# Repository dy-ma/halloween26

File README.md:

# Halloween 2026

The integrated wireless show controller, motor-node firmware, simulator, and Pi
control panel live in [`sync/`](sync/README.md). The original sketches remain
available as isolated hardware tests.

Hardware, software, and build notes for our Halloween 2026 props. This repository holds multiple boards and projects; each has its own directory, README, and design status.

## Projects

| Project | Purpose | Status |
|---|---|---|
| [Base controller](base-controller/README.md) | ESP32-C6 controller for the tractor mechanism, with external stepper-driver control, limit inputs, and onboard power conversion | Initial PCB design complete; verification in progress; not hardware-tested |
| [Baby's first PCB](babys-first/README.md) | Small LED board used to learn KiCad | Practice project; not intended for manufacture |
| [FX audio](fx/README.md) | Rust library providing play-a-file-on-a-device, plus a thin CLI for PipeWire and Bluetooth testing | Initial programmable primitive |
| [Cue firmware](firmware/README.md) | Shared cue messages and non-blocking ESP-NOW transport for button nodes and the Pi serial gateway | Initial refactor; hardware verification pending |

Additional boards can be added alongside these when ready. See [adding a board](docs/adding-a-board.md) for the directory convention.

## Repository layout

```text
halloween26/
├── README.md                 Project index
├── docs/                     Shared repository and release conventions
├── base-controller/
│   ├── README.md             Board overview and status
│   ├── CHANGELOG.md          Board revision notes
│   ├── *.kicad_*             Editable KiCad design
│   ├── docs/                 Architecture, parts, checks, and design history
│   ├── libraries/            Board-specific symbols and footprints
│   ├── previews/             Selected design images
│   └── scripts/              Board-specific build helpers
├── babys-first/              KiCad practice board
├── LICENSE                   Original hardware/design-documentation license
├── LICENSES/                 Additional license texts
└── NOTICE.md                 Attribution and third-party terms
```

Board-specific decisions and instructions belong with that board. The root `docs/` folder is for guidance shared across projects. Open a board's README for its KiCad version, pinouts, build commands, and verification status.

## Releases

Editable sources live in Git. Gerbers, drill files, and other generated manufacturing files are attached manually to [GitHub Releases](https://github.com/dy-ma/halloween26/releases), using board-specific tags such as `base-controller-v0.1.0`. There are no automatic release workflows.

See [the shared release conventions](docs/releases.md) and each board's release instructions. A design being present here does not mean it is ready to manufacture; check that project's status first.

## License

Original hardware and design documentation: [CERN-OHL-P-2.0](LICENSE). Original scripts: [MIT](LICENSES/MIT.txt). Imported libraries retain their upstream terms; see [NOTICE.md](NOTICE.md).

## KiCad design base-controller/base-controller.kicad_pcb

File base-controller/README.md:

# Base controller — tractor motion control

A KiCad learning project for a wireless, chain-driven Halloween tractor prop. A Seeed XIAO ESP32-C6 controls an external DM542-class stepper driver, reads two limit switches, and exposes spare I/O and test points. The board includes 24 V power distribution, a protected logic branch, and a 24 V-to-5 V converter.

**Initial design complete; verification in progress. Not ready to order.** The 92 × 69 mm, two-layer PCB is routed. Checks on 2026-09-20 report zero ERC issues, zero unconnected PCB items, and zero schematic/PCB mismatches. PCB DRC also passes with zero errors or warnings after updating U3’s thermal-via footprint. There has been no hardware bring-up. See the [verification checklist](docs/verification.md).

## Open the design

Use **KiCad 9.0.6** with its standard symbol and footprint libraries installed. Open [base-controller.kicad_pro](base-controller.kicad_pro) in KiCad's project manager, then open the schematic or PCB.

Project-local `Halloween` libraries are registered through checked-in, project-relative library tables. No global custom-library setup should be needed. Some parts lack 3D models; that does not mean their PCB footprint is missing.

| Directory | Contents |
|---|---|
| [`docs/`](docs/) | Architecture, parts, decisions, verification, and release procedure |
| [`docs/history/`](docs/history/) | Earlier schematic, placement, and routing notes |
| [`libraries/`](libraries/) | Project-local symbols and footprints with provenance |
| [`previews/`](previews/) | Selected board and layout images |
| [`scripts/`](scripts/) | Optional local KiCad checks and manufacturing export helper |

See the [board changelog](CHANGELOG.md) for revision notes and the [repository overview](../README.md) for other boards.

## Design reference

- [Architecture, connector pinouts, GPIO map, and rationale](docs/architecture.md)
- [Parts list and JLC links](docs/parts-list.md)
- [Power protection and driver-interface decisions](docs/electrical-decisions.md)
- [External power supplies, inline fuse, and cable recommendations](docs/non-pcb-components.md)
- [Library provenance and changes](libraries/README.md)
- [Sourcing research](docs/parts-sourcing.md) — dated stock snapshots, including superseded candidates
- [Historical schematic review](docs/history/schematic-review-notes.md) — not the current issue list

The controller uses **24 V nominal input**. Motor supply power passes through to J7; the onboard eFuse protects the logic branch only. Remove **J6** before using USB with external power. The DM542 driver, motor, power supply, inline fuse, mechanics, firmware, and audio controller are external to this PCB. The 5 A pass-through figure is a design target, not a tested rating.

## Checks and releases

Save the project, then optionally run **from the repository root**:

```sh
python3 base-controller/scripts/build_hardware.py check
```

This checks a copy, refills zones, runs ERC/DRC and schematic parity, and produces review files under `build/base-controller/check/`. The current design passes these automated checks; the manual verification checklist still applies. It does not modify your KiCad sources.

Gerbers and drill files belong in **GitHub Releases**, not the source tree. Releases are prepared manually; there is no GitHub Actions workflow. Follow [the release procedure](docs/releases.md) to use either KiCad's GUI or the local script, inspect the outputs, and attach ZIPs to a tagged release.

The printed QR code points to [the future project article](https://www.dyma.dev/articles/tractor-driver).

## License

Original hardware and design documentation: [CERN-OHL-P-2.0](../LICENSE). Original scripts: [MIT](../LICENSES/MIT.txt). Imported library material keeps its upstream licenses; see [NOTICE.md](../NOTICE.md).

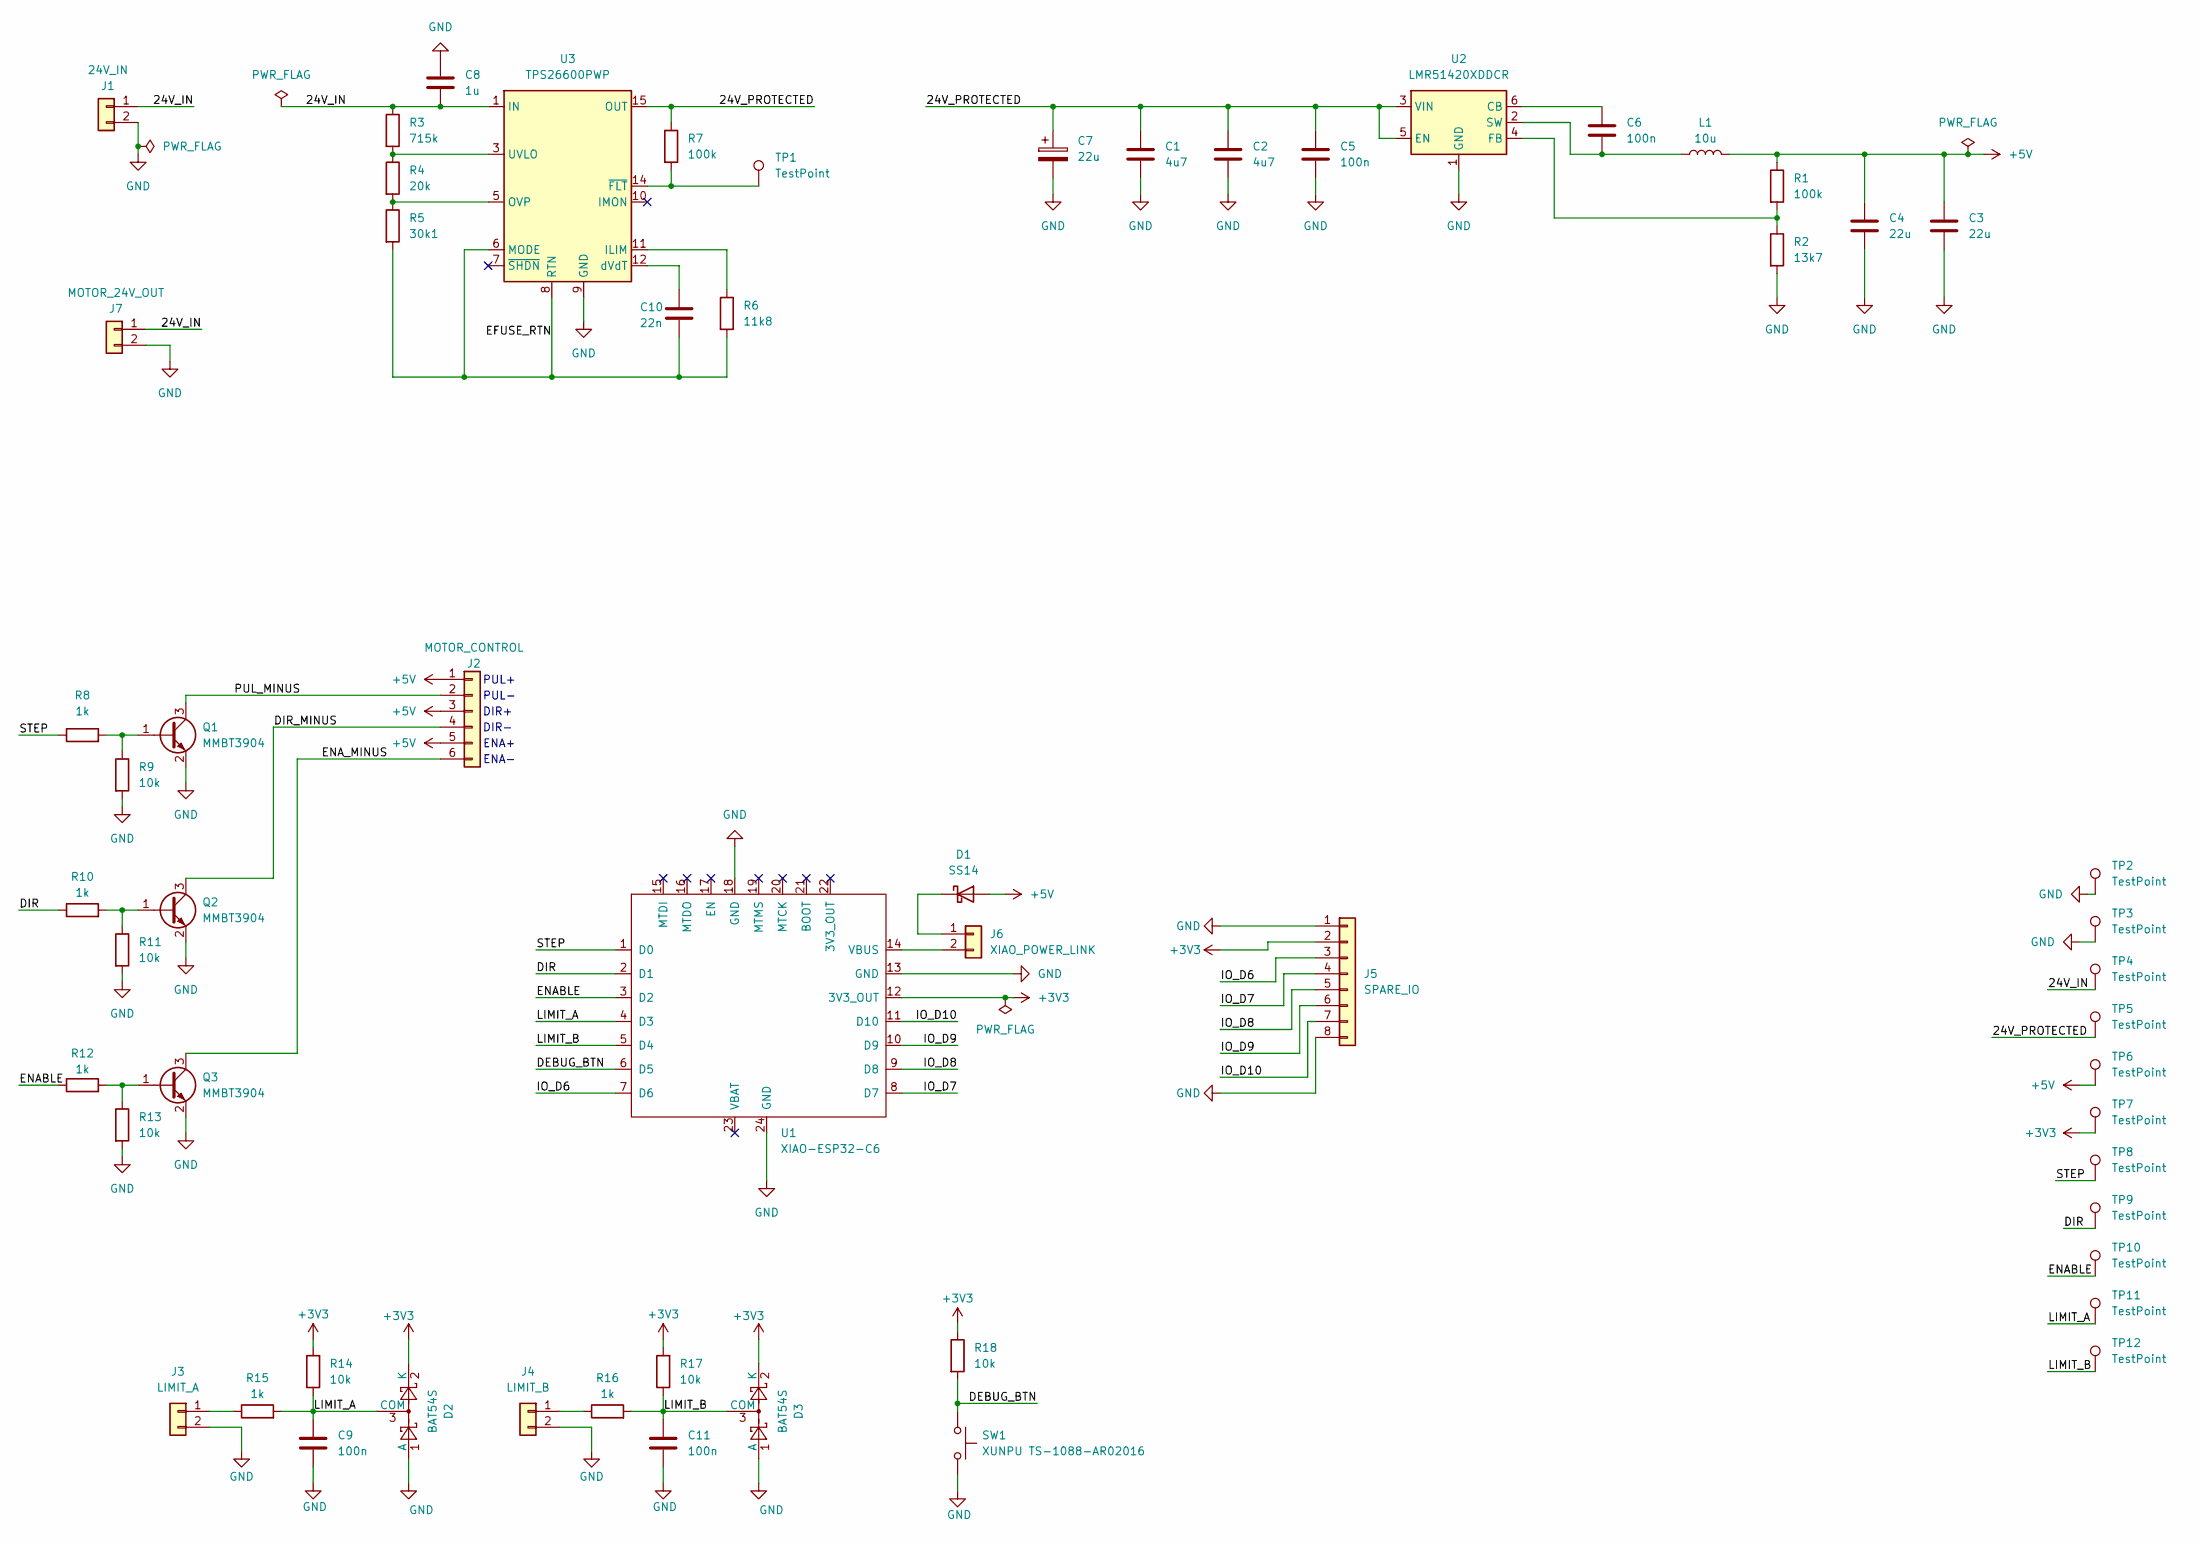
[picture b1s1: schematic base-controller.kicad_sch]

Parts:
C1, C2: 4u7; C_1206_3216Metric; MPN CL31B475KBHNNNE; LCSC C51205
C3, C4: 22u; C_1206_3216Metric; MPN CL31A226KAHNNNE; LCSC C12891
C5, C6, C9, C11: 100n; C_0603_1608Metric; MPN CC0603KRX7R9BB104; LCSC C14663
C7: 22u; CP_Elec_6.3x5.4; MPN RVT1H220M0605; LCSC C27783
C8: 1u; C_0805_2012Metric; MPN CL21B105KBFNNNE; LCSC C28323
C10: 22n; C_0603_1608Metric; MPN CL10B223KB8NNNC; LCSC C21122
D1: SS14; D_SMA; MPN SS14; LCSC C2480
D2, D3: BAT54S; SOT-23; MPN BAT54S KL4; LCSC C8592
J1: 24V_IN; Molex_Micro-Fit_3.0_43650-0215_1x02_P3.00mm_Vertical; MPN 436500215; LCSC C293740
J2: MOTOR_CONTROL; JST_XH_S6B-XH-A_1x06_P2.50mm_Horizontal; MPN S6B-XH-A(LF)(SN); LCSC C157919
J3: LIMIT_A; JST_XH_S2B-XH-A_1x02_P2.50mm_Horizontal; MPN S2B-XH-A(LF)(SN); LCSC C157931
J4: LIMIT_B; JST_XH_S2B-XH-A_1x02_P2.50mm_Horizontal; MPN S2B-XH-A(LF)(SN); LCSC C157931
J5: SPARE_IO; PinHeader_1x08_P2.54mm_Vertical; MPN PZ254V-11-08P; LCSC C492407
J6: XIAO_POWER_LINK; PinHeader_1x02_P2.54mm_Vertical; MPN PZ254V-11-02P; LCSC C492401
J7: MOTOR_24V_OUT; Molex_Micro-Fit_3.0_43650-0215_1x02_P3.00mm_Vertical; MPN 436500215; LCSC C293740
L1: 10u; L_Sunlord_MWSA0804S; MPN MWSA0804S-100MT; LCSC C17700171
Q1, Q2, Q3: MMBT3904; SOT-23; MPN MMBT3904(RANGE:100-300); LCSC C20526
R1, R7: 100k; R_0603_1608Metric; MPN 0603WAF1003T5E; LCSC C25803
R2: 13k7; R_0603_1608Metric; MPN 0603WAF1372T5E; LCSC C22793
R3: 715k; R_0603_1608Metric; MPN RC0603FR-07715KL; LCSC C137685
R4: 20k; R_0603_1608Metric; MPN 0603WAF2002T5E; LCSC C4184
R5: 30k1; R_0603_1608Metric; MPN 0603WAF3012T5E; LCSC C23000
R6: 11k8; R_0603_1608Metric; MPN 0603WAF1182T5E; LCSC C22861
R8, R10, R12, R15, R16: 1k; R_0603_1608Metric; MPN 0603WAF1001T5E; LCSC C21190
R9, R11, R13, R14, R17, R18: 10k; R_0603_1608Metric; MPN 0603WAF1002T5E; LCSC C25804
SW1: XUNPU TS-1088-AR02016; SW_SPST_TS-1088-xR020; MPN TS-1088-AR02016; LCSC C720477
TP1, TP2, TP3, TP4, TP5, TP6, TP7, TP8, TP9, TP10, TP11, TP12: TestPoint; TestPoint_Pad_D2.0mm
U1: XIAO-ESP32-C6; XIAO-ESP32-C6-SMD; MPN 113991254; LCSC C27675191
U2: LMR51420XDDCR; TSOT-23-6; MPN LMR51420XDDCR; LCSC C5246146
U3: TPS26600PWP; TPS26600_HTSSOP16_ThermalVias_0.3mm; MPN TPS26600PWPR; LCSC C544399

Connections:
+3V3: D2.2 (K), D3.2 (K), J5.2, R14.2, R17.2, R18.1, TP7.1, U1.12 (3V3_OUT)
+5V: C3.1, C4.1, D1.2 (A), J2.1, J2.3, J2.5, L1.2, R1.1, TP6.1
/24V_IN: C8.1, J1.1, J7.1, R3.1, TP4.1, U3.1 (IN), U3.2 (IN)
/24V_PROTECTED: C1.1, C2.1, C5.1, C7.1, R7.1, TP5.1, U2.3 (VIN), U2.5 (EN), U3.15 (OUT), U3.16 (OUT)
/DEBUG_BTN: R18.2, SW1.1, U1.6 (D5)
/DIR: R10.1, TP9.1, U1.2 (D1)
/DIR_MINUS: J2.4, Q2.3 (C)
/EFUSE_RTN: C10.2, R5.2, R6.2, U3.6 (MODE), U3.8 (RTN), U3.17 (RTN)
/ENABLE: R12.1, TP10.1, U1.3 (D2)
/ENA_MINUS: J2.6, Q3.3 (C)
/IO_D6: J5.3, U1.7 (D6)
/IO_D7: J5.4, U1.8 (D7)
/IO_D8: J5.5, U1.9 (D8)
/IO_D9: J5.6, U1.10 (D9)
/IO_D10: J5.7, U1.11 (D10)
/LIMIT_A: C9.1, D2.3 (COM), R14.1, R15.2, TP11.1, U1.4 (D3)
/LIMIT_B: C11.1, D3.3 (COM), R16.2, R17.1, TP12.1, U1.5 (D4)
/PUL_MINUS: J2.2, Q1.3 (C)
/STEP: R8.1, TP8.1, U1.1 (D0)
GND: C1.2, C2.2, C3.2, C4.2, C5.2, C7.2, C8.2, C9.2, C11.2, D2.1 (A), D3.1 (A), J1.2, J3.2, J4.2, J5.1, J5.8, J7.2, Q1.2 (E), Q2.2 (E), Q3.2 (E), R2.2, R9.2, R11.2, R13.2, SW1.2, TP2.1, TP3.1, U1.13 (GND), U1.18 (GND), U1.24 (GND), U2.1 (GND), U3.9 (GND)
unnamed: D1.1 (K), J6.1
unnamed: J3.1, R15.1
unnamed: J4.1, R16.1
unnamed: J6.2, U1.14 (VBUS)
unnamed: Q1.1 (B), R8.2, R9.1
unnamed: Q2.1 (B), R10.2, R11.1
unnamed: Q3.1 (B), R12.2, R13.1
unnamed: C6.1, U2.6 (CB)
unnamed: R1.2, R2.1, U2.4 (FB)
unnamed: C6.2, L1.1, U2.2 (SW)
unnamed: R6.1, U3.11 (ILIM)
unnamed: R4.2, R5.1, U3.5 (OVP)
unnamed: R3.2, R4.1, U3.3 (UVLO)
unnamed: C10.1, U3.12 (dVdT)
unnamed: R7.2, TP1.1, U3.14 (~FLT)

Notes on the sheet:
ENA-
PUL+
DIR+
PUL-
DIR-
ENA+

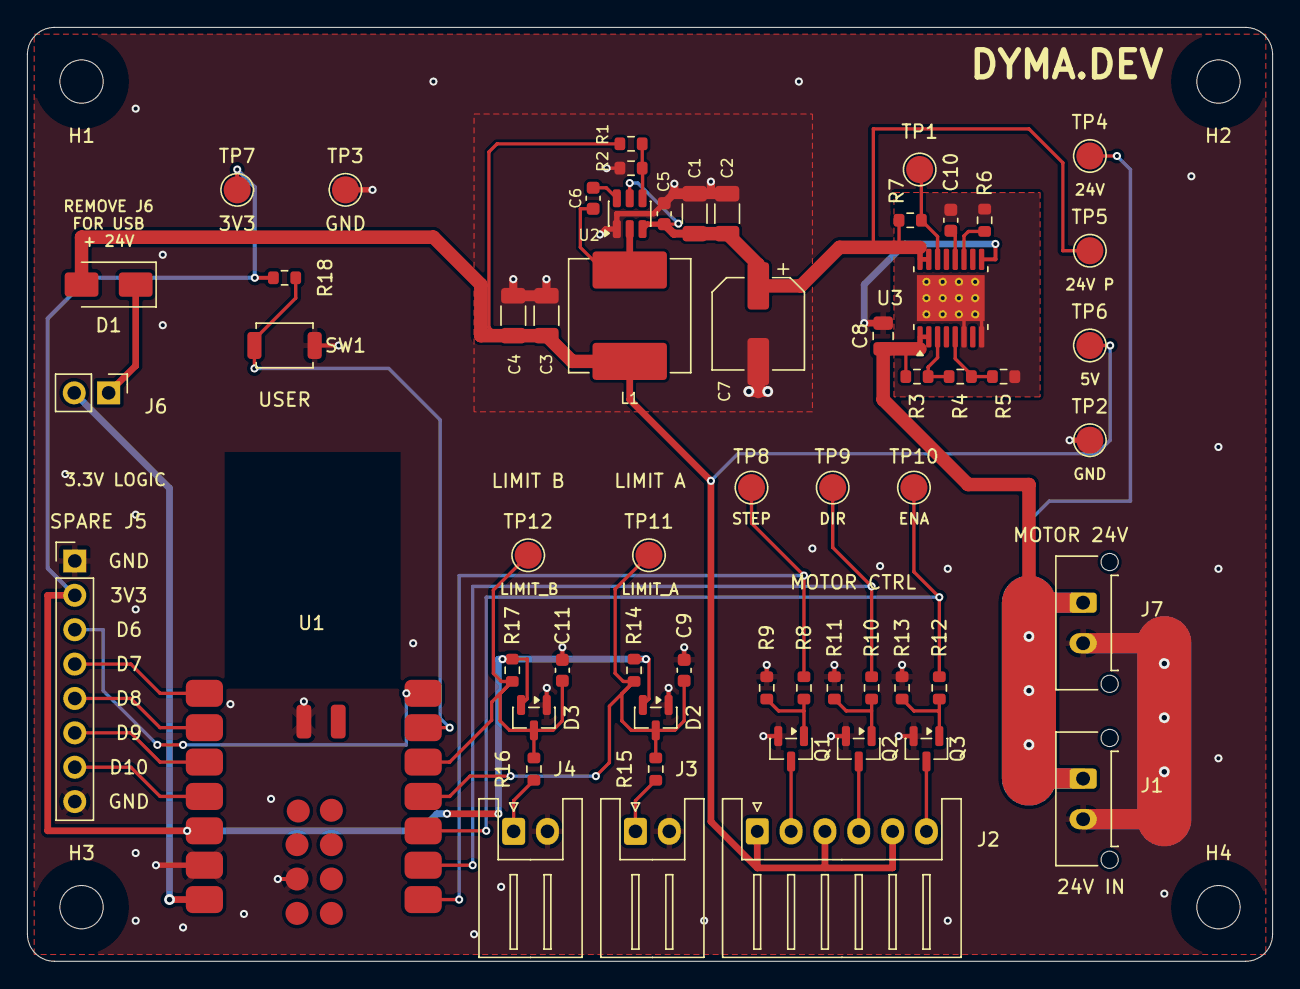
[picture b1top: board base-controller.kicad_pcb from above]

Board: 2 copper layers, 92.0 x 69.0 mm, 64 parts (1 on the bottom side), 35 nets.

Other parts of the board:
H1, H2, H3, H4: MountingHole_3.2mm_M3
QR1: https://www.dyma.dev/articles/tractor-driver; QR_TractorDriver

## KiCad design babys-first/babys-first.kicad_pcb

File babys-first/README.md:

# Baby's first PCB

A small LED/resistor practice board used to learn KiCad schematic capture, footprints, routing, silkscreen, and Gerber export. It is not the tractor controller and was not intended for manufacture.

Open `babys-first.kicad_pro` in KiCad. This project was originally named `tractor-driver`; the current name reflects its role as a learning exercise. The hardware release script targets only `base-controller/`.

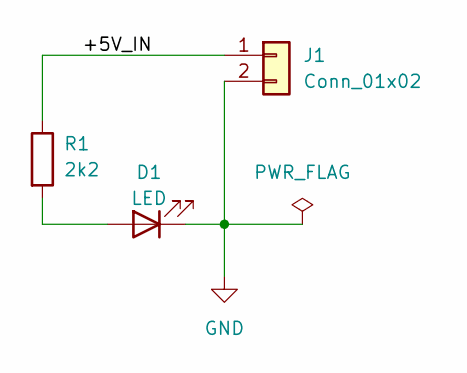
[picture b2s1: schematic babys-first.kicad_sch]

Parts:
D1: LED; LED_0805_2012Metric
J1: Conn_01x02; PinHeader_1x02_P2.54mm_Vertical_SMD_Pin1Left
R1: 2k2; R_0805_2012Metric

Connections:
/+5V_IN: J1.1, R1.1
GND: D1.1 (K), J1.2
unnamed: D1.2 (A), R1.2

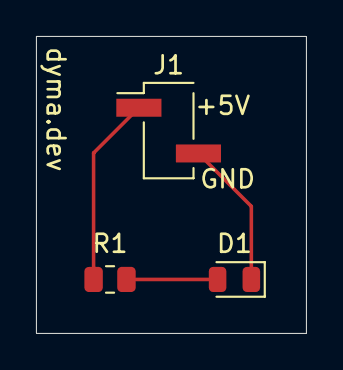
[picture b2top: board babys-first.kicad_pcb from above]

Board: 2 copper layers, 15.0 x 16.5 mm, 3 parts (0 on the bottom side), 3 nets.
